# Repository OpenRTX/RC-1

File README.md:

# RadioCard 1 (RC-1)

radio modem in a M.2 form factor.

## Block diagram

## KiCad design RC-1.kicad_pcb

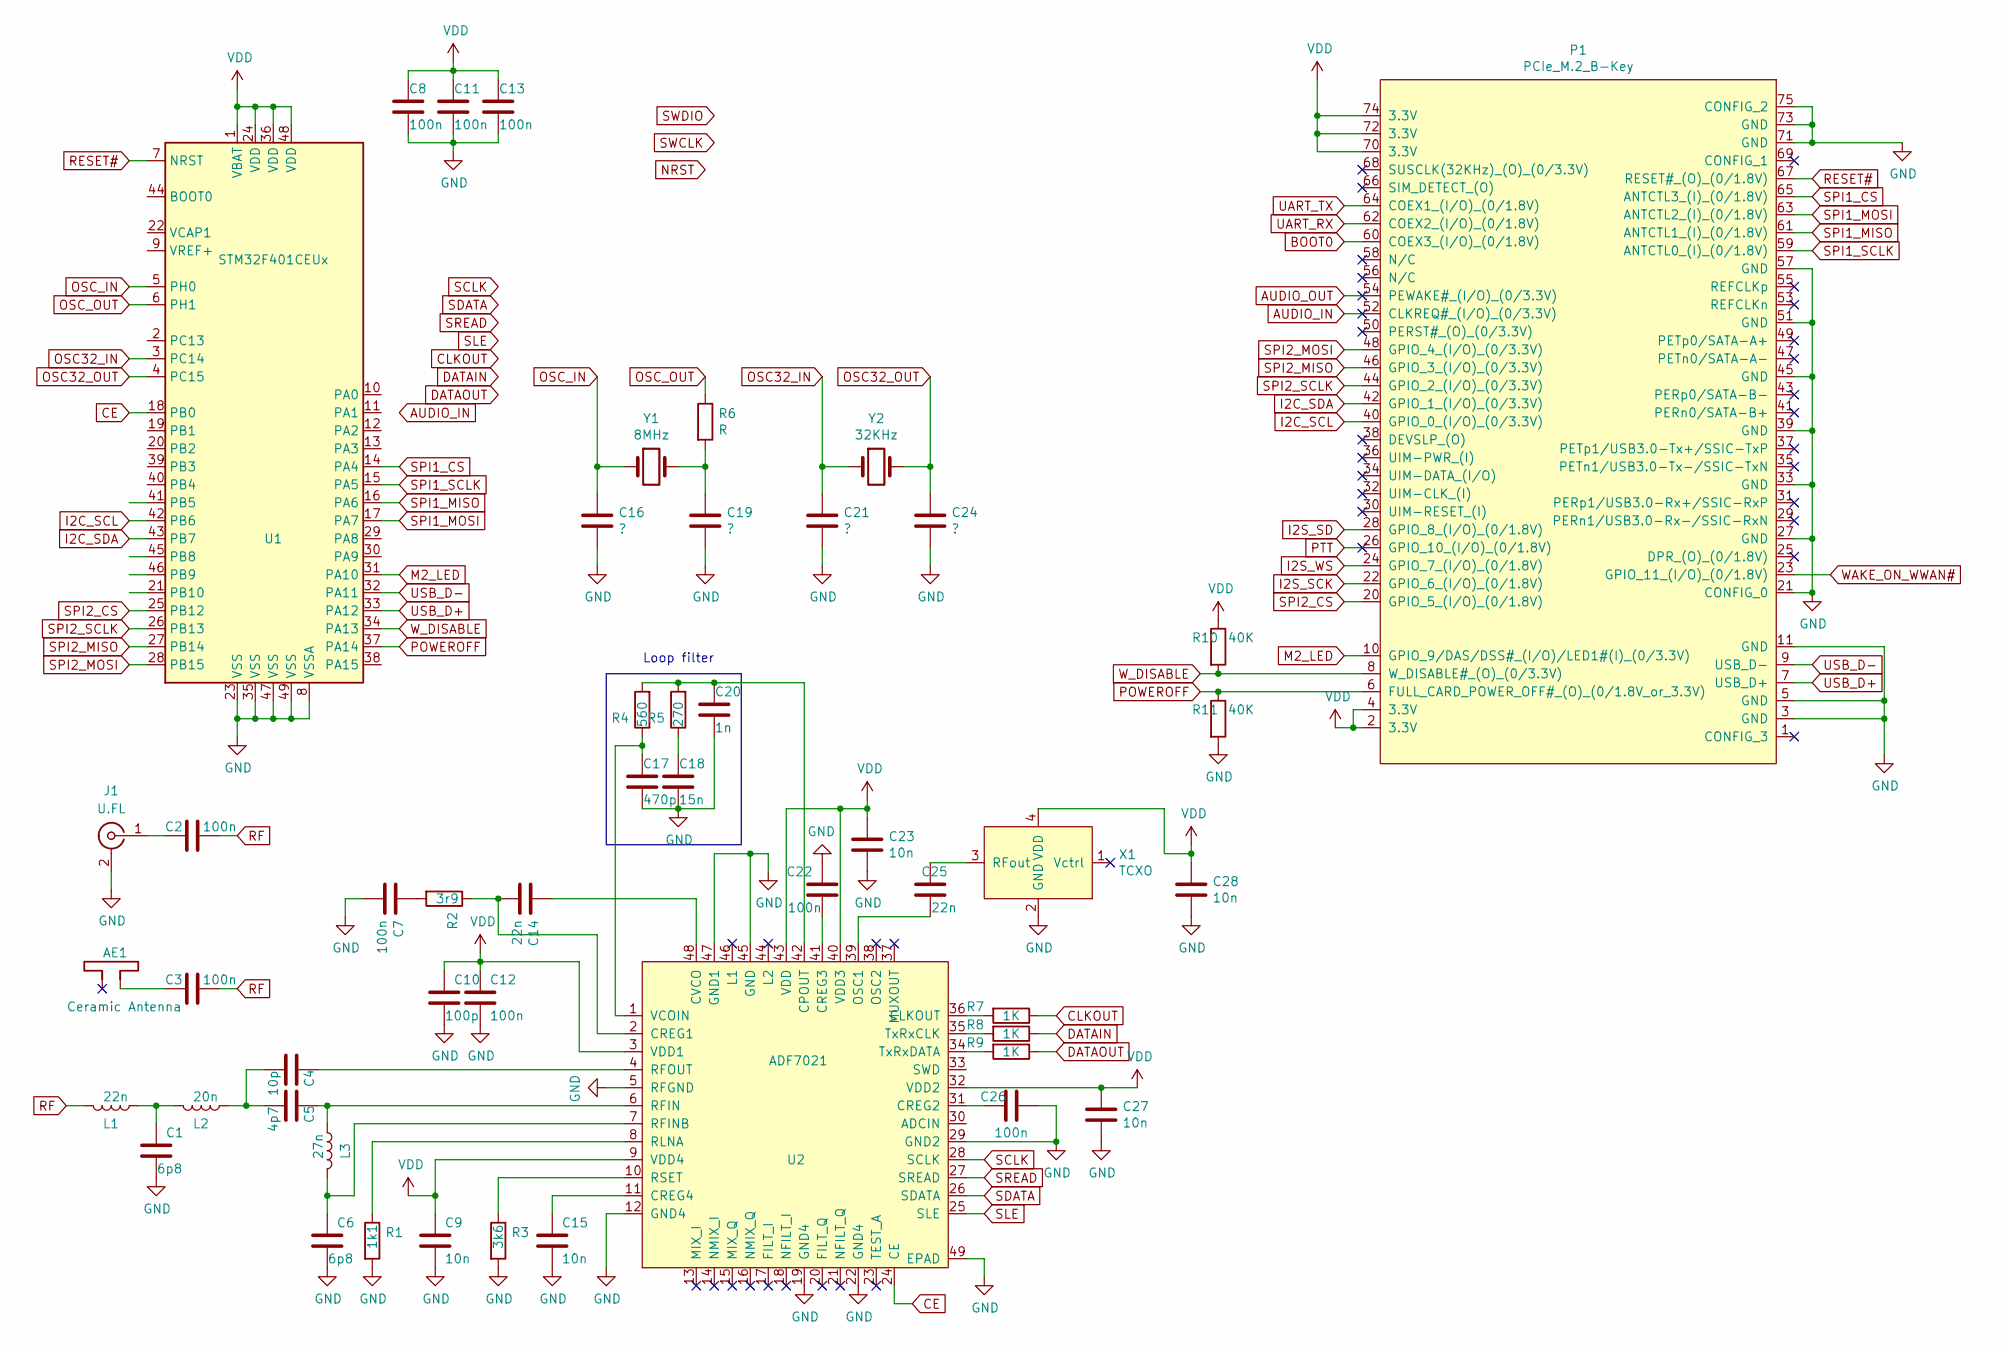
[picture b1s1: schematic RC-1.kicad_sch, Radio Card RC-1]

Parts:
AE1: Ceramic Antenna
C1, C6: 6p8; C_0402_1005Metric
C2, C3, C7, C8, C11, C12, C13, C22, C26: 100n; C_0402_1005Metric
C4: 10p; C_0402_1005Metric
C5: 4p7; C_0402_1005Metric
C9, C15, C23, C27, C28: 10n; C_0402_1005Metric
C10: 100p; C_0402_1005Metric
C14, C25: 22n; C_0402_1005Metric
C16, C19, C21, C24: ?; C_0402_1005Metric
C17: 470p; C_0402_1005Metric
C18: 15n; C_0402_1005Metric
C20: 1n; C_0402_1005Metric
J1: U.FL; U.FL_Hirose_U.FL-R-SMT-1_Vertical
L1: 22n; L_0402_1005Metric
L2: 20n; L_0402_1005Metric
L3: 27n; L_0402_1005Metric
P1: PCIe_M.2_B-Key; NGFF_B
R1: 1k1; R_0402_1005Metric
R2: 3r9; R_0402_1005Metric
R3: 3k6; R_0402_1005Metric
R4: 560; R_0402_1005Metric
R5: 270; R_0402_1005Metric
R6: R; R_01005_0402Metric
R7, R8, R9: 1K; R_0402_1005Metric
R10, R11: 40K; R_0402_1005Metric
U1: STM32F401CEUx; QFN-48-1EP_7x7mm_P0.5mm_EP5.6x5.6mm
U2: ADF7021; LFCSP-48-1EP_7x7mm_P0.5mm_EP4.1x4.1mm
X1: TCXO
Y1: 8MHz
Y2: 32KHz

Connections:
AUDIO_IN: P1.52 (CLKREQ#_(I/O)_(0/3.3V))
AUDIO_OUT: P1.54 (PEWAKE#_(I/O)_(0/3.3V))
BOOT0: P1.60 (COEX3_(I/O)_(0/1.8V))
CE: U1.18 (PB0), U2.24 (CE)
CLKOUT: R7.1
DATAIN: R8.1
DATAOUT: R9.1
GND: C1.2, C6.2, C7.2, C8.2, C9.2, C10.2, C11.2, C12.2, C13.2, C15.2, C16.2, C17.2, C18.2, C19.2, C20.2, C21.2, C22.2, C23.2, C24.2, C26.1, C27.2, C28.2, J1.2 (Ext), P1.3 (GND), P1.5 (GND), P1.11 (GND), P1.21 (CONFIG_0), P1.27 (GND), P1.33 (GND), P1.39 (GND), P1.45 (GND), P1.51 (GND), P1.57 (GND), P1.71 (GND), P1.73 (GND), P1.75 (CONFIG_2), R1.2, R3.2, R11.2, U1.8 (VSSA), U1.23 (VSS), U1.35 (VSS), U1.47 (VSS), U1.49 (VSS), U2.5 (RFGND), U2.12 (GND4), U2.19 (GND4), U2.22 (GND4), U2.29 (GND2), U2.45 (GND), U2.47 (GND1), U2.49 (EPAD), X1.2 (GND)
I2C_SCL: P1.40 (GPIO_0_(I/O)_(0/3.3V)), U1.42 (PB6)
I2C_SDA: P1.42 (GPIO_1_(I/O)_(0/3.3V)), U1.43 (PB7)
I2S_SCK: P1.22 (GPIO_6_(I/O)_(0/1.8V))
I2S_SD: P1.28 (GPIO_8_(I/O)_(0/1.8V))
I2S_WS: P1.24 (GPIO_7_(I/O)_(0/1.8V))
M2_LED: P1.10 (GPIO_9/DAS/DSS#_(I/O)/LED1#(I)_(0/3.3V)), U1.31 (PA10)
unnamed: AE1.2, C3.1
unnamed: C1.1, L1.1, L2.2
unnamed: C2.1, J1.1 (In)
unnamed: C4.1, C5.1, L2.1
unnamed: C4.2, U2.4 (RFOUT)
unnamed: C5.2, L3.1, U2.6 (RFIN)
unnamed: C6.1, L3.2, U2.7 (RFINB)
unnamed: C7.1, R2.2
unnamed: C14.1, U2.48 (CVCO)
unnamed: C14.2, R2.1, U2.2 (CREG1)
unnamed: C15.1, U2.11 (CREG4)
unnamed: C17.1, R4.1, U2.1 (VCOIN)
unnamed: C18.1, R5.1
unnamed: C19.1, R6.2, Y1.2
unnamed: C20.1, R4.2, R5.2, U2.42 (CPOUT)
unnamed: C22.1, U2.41 (CREG3)
unnamed: C25.1, U2.39 (OSC1)
unnamed: C25.2, X1.3 (RFout)
unnamed: C26.2, U2.31 (CREG2)
unnamed: R1.1, U2.8 (RLNA)
unnamed: R3.1, U2.10 (RSET)
unnamed: R7.2, U2.36 (CLKOUT)
unnamed: R8.2, U2.35 (TxRxCLK)
unnamed: R9.2, U2.34 (TxRxDATA)
OSC32_IN: C21.1, U1.3 (PC14), Y2.1
OSC32_OUT: C24.1, U1.4 (PC15), Y2.2
OSC_IN: C16.1, U1.5 (PH0), Y1.1
OSC_OUT: R6.1, U1.6 (PH1)
POWEROFF: P1.6 (FULL_CARD_POWER_OFF#_(O)_(0/1.8V_or_3.3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), R11.1, U1.37 (PA14)
PTT: P1.26 (GPIO_10_(I/O)_(0/1.8V))
RESET#: P1.67 (RESET#_(O)_(0/1.8V)), U1.7 (NRST)
RF: C2.2, C3.2, L1.2
SCLK: U2.28 (SCLK)
SDATA: U2.26 (SDATA)
SLE: U2.25 (SLE)
SPI1_CS: P1.65 (ANTCTL3_(I)_(0/1.8V)), U1.14 (PA4)
SPI1_MISO: P1.61 (ANTCTL1_(I)_(0/1.8V)), U1.16 (PA6)
SPI1_MOSI: P1.63 (ANTCTL2_(I)_(0/1.8V)), U1.17 (PA7)
SPI1_SCLK: P1.59 (ANTCTL0_(I)_(0/1.8V)), U1.15 (PA5)
SPI2_CS: P1.20 (GPIO_5_(I/O)_(0/1.8V)), U1.25 (PB12)
SPI2_MISO: P1.46 (GPIO_3_(I/O)_(0/3.3V)), U1.27 (PB14)
SPI2_MOSI: P1.48 (GPIO_4_(I/O)_(0/3.3V)), U1.28 (PB15)
SPI2_SCLK: P1.44 (GPIO_2_(I/O)_(0/3.3V)), U1.26 (PB13)
SREAD: U2.27 (SREAD)
UART_RX: P1.62 (COEX2_(I/O)_(0/1.8V))
UART_TX: P1.64 (COEX1_(I/O)_(0/1.8V))
USB_D+: P1.7 (USB_D+), U1.33 (PA12)
USB_D-: P1.9 (USB_D-), U1.32 (PA11)
VDD: C8.1, C9.1, C10.1, C11.1, C12.1, C13.1, C23.1, C27.1, C28.1, P1.2 (3.3V), P1.4 (3.3V), P1.70 (3.3V), P1.72 (3.3V), P1.74 (3.3V), R10.1, U1.1 (VBAT), U1.24 (VDD), U1.36 (VDD), U1.48 (VDD), U2.3 (VDD1), U2.9 (VDD4), U2.32 (VDD2), U2.40 (VDD3), U2.43 (VDD), X1.4 (VDD)
WAKE_ON_WWAN#: P1.23 (GPIO_11_(I/O)_(0/1.8V))
W_DISABLE: P1.8 (W_DISABLE#_(O)_(0/3.3V)), R10.2, U1.34 (PA13)

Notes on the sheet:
Loop filter

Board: 4 copper layers, 46 parts (0 on the bottom side), 46 nets, no tracks yet.

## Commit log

2021-08-03 Create LICENSE
2021-12-29 Add old changes from 3 Aug 2021
2021-12-29 Migrated project to Kicad 6.0, add gitignore to avoid committing backups
2021-12-29 Set project title and add PDF schematic
2021-12-30 Set up PCB for M.2 Type 3042-S3 form factor.
2021-12-30 Add block diagram, moved schematic and block diagram to documentation subfolder
2021-12-30 Fix typo in README image link
2021-12-30 Updated block diagram
2021-12-30 Added missing SWD connection to block diagram
2021-12-30 Pin mapping for ATSAMD51G18A MCU
2021-12-30 Added missing T/R switch control to ATSAMD51G18A pin mapping
2021-12-31 Split schematic into 3 sheets: connectors, mcu and radio
2021-12-31 Reorganised ATSAMD51G18A pin mapping to add connections for 32kHz crystal
2021-12-31 Replaced STM32 with ATSAMD51G
2021-12-31 Modified ATSAMD51G18A pin mapping to add VBAT on PB3 and WWAN_DISABLE signal
2021-12-31 Changed MCU and M.2 pin assignment
2021-12-31 Add SOICbite SWD+UART connector
2022-01-01 Aligned pin mapping with schematic
2022-01-01 Schematic revision, details below.
    [M.2 connector]
    - Disconnected NRESET signal from pin 67 (RESET#_(O)_(O/1.8V)) as this would have caused a dangerous back-feed of 3.3V in a signal specified for 1.8V
    - Moved I2S_FS signal to pin 26 to group it together the other I2S lines.
    - Moved USART signals to pins 40 and 42.
    - Moved I2C signals to pins 44 and 46.
    - Replaced VBAT global label with '+BATT' power symbol.
2022-01-01 Add MCU to ADF7021 connection
2022-01-02 Added interfacing transistors for LED and nRESET signals on M.2 connector, switched from global to hierarchical net labels
2022-01-03 Aligned ADF7021 wiring to TR-9 schematic
2022-01-03 Moved resistor values outside of symbols
2022-01-04 Split PC_DETECT and POWER_OFF lines
2022-01-05 Connected ADF7021 chip enable to MCU, grouped PTT/W_DISABLE signal with SWDIO
2022-01-05 Added I2C for external EEPROM on the M.2 connector, added pull-up resistors on the I2C lines
2022-01-06 Set up ADF7021 for single RF output, 2-point modulation
2022-01-06 Replaced U.FL RF connector with MHF4
2022-01-06 Set all SMD passive size to 0402
2022-01-17 Added DAC for PA/preselector bias voltage
